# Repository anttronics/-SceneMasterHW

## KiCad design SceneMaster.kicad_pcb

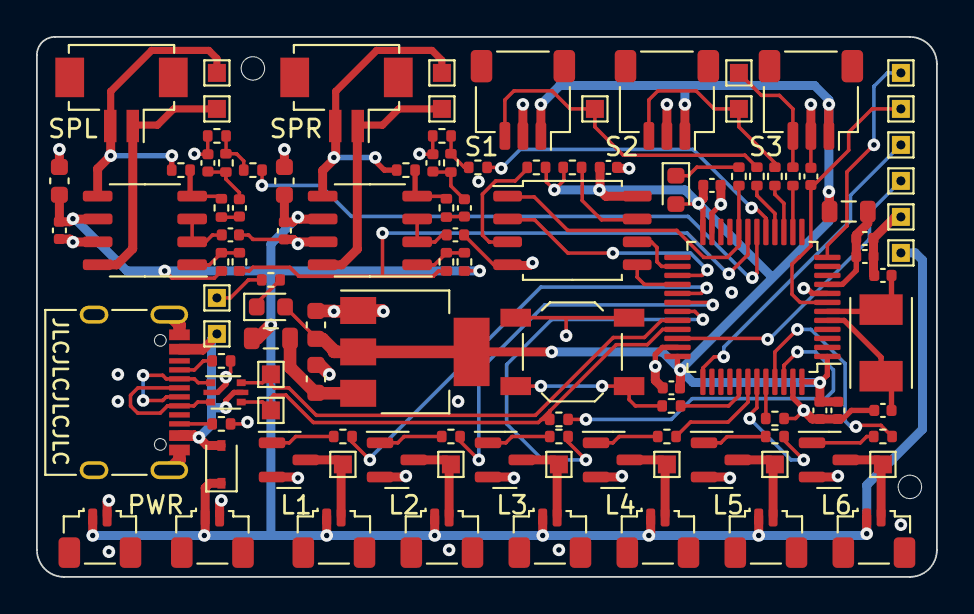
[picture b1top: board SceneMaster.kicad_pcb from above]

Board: 4 copper layers, 50.0 x 30.0 mm, 110 parts (0 on the bottom side), 73 nets.

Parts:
C1, C2: 20p; C_0402_1005Metric
C3, C4, C5, C9, C11, C13, C15: 100n; C_0402_1005Metric
C6, C12: 10u; C_0402_1005Metric
C7: 10n; C_0402_1005Metric
C8, C10: 470n; C_0402_1005Metric
C14, C16, C21, C22: 22u; C_0603_1608Metric
C17, C18, C19, C20: 2.2u; C_0402_1005Metric
D1: 1N5819WS; D_SOD-323
D2: LED Blue; LED_0603_1608Metric
D3: LED Red; LED_0603_1608Metric
FB1, FB2: 100Ω@100MHz; L_0805_2012Metric
J1: TYPE-C-31-M-12; USB_C_Receptacle_XKB_U262-16XN-4BVC11
J2: SPK_R; Hirose_DF13C_CL535-0402-2-51_1x02-1MP_P1.25mm_Vertical
J3: LED1; JST_SUR_SM02B-SURS-TF_1x02-1MP_P0.80mm_Horizontal
J4: LED2; JST_SUR_SM02B-SURS-TF_1x02-1MP_P0.80mm_Horizontal
J5: LED6; JST_SUR_SM02B-SURS-TF_1x02-1MP_P0.80mm_Horizontal
J6: Sensor3; JST_SH_SM03B-SRSS-TB_1x03-1MP_P1.00mm_Horizontal
J7: Sensor1; JST_SH_SM03B-SRSS-TB_1x03-1MP_P1.00mm_Horizontal
J8: Sensor2; JST_SH_SM03B-SRSS-TB_1x03-1MP_P1.00mm_Horizontal
J9: SPK_L; Hirose_DF13C_CL535-0402-2-51_1x02-1MP_P1.25mm_Vertical
J11: PowerIn; JST_SUR_SM02B-SURS-TF_1x02-1MP_P0.80mm_Horizontal
J12: PowerOut; JST_SUR_SM02B-SURS-TF_1x02-1MP_P0.80mm_Horizontal
J13: LED3; JST_SUR_SM02B-SURS-TF_1x02-1MP_P0.80mm_Horizontal
J14: LED4; JST_SUR_SM02B-SURS-TF_1x02-1MP_P0.80mm_Horizontal
J15: LED5; JST_SUR_SM02B-SURS-TF_1x02-1MP_P0.80mm_Horizontal
Q1, Q2, Q3, Q4, Q5, Q6: AO3400A; SOT-23
R1, R2: 5k1; R_0402_1005Metric
R3, R4, R5, R6, R7, R12, R13, R15, R16, R17, R18, R22, R26, R27, R28, R29, R30, R31, R32: 1k5; R_0402_1005Metric
R8, R9: 75R; R_0402_1005Metric
R10, R11, R14, R19, R23: 100k; R_0402_1005Metric
R20, R24: 20k; R_0402_1005Metric
R21, R25: 33k; R_0402_1005Metric
SW1: BUT0; SW_SPST_TL3342
TP1: SENS1; TestPoint_Pad_1.0x1.0mm
TP2: SENS2; TestPoint_Pad_1.0x1.0mm
TP3: SWDIO; TestPoint_THTPad_1.0x1.0mm_Drill0.5mm
TP4: SWCLK; TestPoint_THTPad_1.0x1.0mm_Drill0.5mm
TP5: UARTTX; TestPoint_THTPad_1.0x1.0mm_Drill0.5mm
TP6: D-; TestPoint_Pad_1.0x1.0mm
TP7: D+; TestPoint_Pad_1.0x1.0mm
TP8: VBUS; TestPoint_THTPad_1.0x1.0mm_Drill0.5mm
TP9, TP20: GND; TestPoint_THTPad_1.0x1.0mm_Drill0.5mm
TP10: SENS3; TestPoint_Pad_1.0x1.0mm
TP11: LED1; TestPoint_Pad_1.0x1.0mm
TP12: LED2; TestPoint_Pad_1.0x1.0mm
TP13: LED6; TestPoint_Pad_1.0x1.0mm
TP14: SPK_R-; TestPoint_Pad_1.0x1.0mm
TP15: SKP_L-; TestPoint_Pad_1.0x1.0mm
TP16: LED3; TestPoint_Pad_1.0x1.0mm
TP17: LED4; TestPoint_Pad_1.0x1.0mm
TP18: LED5; TestPoint_Pad_1.0x1.0mm
TP19: 5V; TestPoint_THTPad_1.0x1.0mm_Drill0.5mm
TP21: SPK_R+; TestPoint_Pad_1.0x1.0mm
TP22: SKP_L+; TestPoint_Pad_1.0x1.0mm
TP23: NRST; TestPoint_THTPad_1.0x1.0mm_Drill0.5mm
U1: USBLC6-2P6; SOT-666
U2: W25Q128JVS; SOIC-8_5.275x5.275mm_P1.27mm
U3: AMS1117-3.3; SOT-223-3_TabPin2
U4: STM32F103C8T6; LQFP-48_7x7mm_P0.5mm
U5, U6: 8002B_D; SOP-8_3.9x4.9mm_P1.27mm
Y1: 8MHz; Crystal_SMD_TXC_7A-2Pin_5x3.2mm

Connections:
+3.3VA: C7.1, C12.1, FB1.2, U4.9 (VDDA)
+3V3: C3.1, C4.1, C5.1, C6.1, C13.1, C16.1, D2.2 (A), D3.2 (A), FB1.1, J6.1, J7.1, J8.1, R10.2, R11.1, U2.8 (VCC), U3.2 (VO), U4.1 (VBAT), U4.24 (VDD), U4.36 (VDD), U4.48 (VDD)
+5V: C17.2, C19.2, C21.1, C22.1, D1.1 (K), FB2.1, J3.1, J4.1, J5.1, J11.1, J12.1, J13.1, J14.1, J15.1, R19.2, R23.2, TP19.1, U5.6 (VDD), U6.6 (VDD)
/BUT0: R3.2, U4.41 (PB5)
/D+: J1.A6 (D+), J1.B6 (D+), U1.3 (I/O2)
/D-: J1.A7 (D-), J1.B7 (D-), U1.1 (I/O1)
/LED1: R26.2, U4.29 (PA8)
/LED2: R27.2, U4.30 (PA9)
/LED3: R29.2, U4.31 (PA10)
/LED4: R30.2, U4.42 (PB6)
/LED5: R31.2, U4.43 (PB7)
/LED6: R28.2, U4.45 (PB8)
/Line_Out_L: C10.1, C11.1, R9.2
/Line_Out_R: C8.1, C9.1, R8.2
/MISO: U2.2 (DO(IO1)), U4.27 (PB14)
/MOSI: U2.5 (DI(IO0)), U4.28 (PB15)
/MUTE: R15.2, R22.2, U4.19 (PB1)
/NRST: C15.2, TP23.1, U4.7 (NRST)
/OSC_IN: C1.1, U4.5 (PD0), Y1.1
/OSC_OUT: C2.1, U4.6 (PD1), Y1.2
/PWM_AUDIO_L: R6.2, U4.18 (PB0)
/PWM_AUDIO_R: R4.2, U4.17 (PA7)
/SCLK: U2.6 (CLK), U4.26 (PB13)
/SENS1: R16.1, U4.16 (PA6)
/SENS2: R17.1, U4.15 (PA5)
/SENS3: R18.1, U4.14 (PA4)
/SPI_CS: R12.1, U2.1 (~CS), U4.20 (PB2)
/SPK_L+: J9.2, R25.2, TP22.1, U6.5 (OUT+)
/SPK_L-: J9.1, TP15.1, U6.8 (OUT-)
/SPK_R+: J2.2, R21.2, TP21.1, U5.5 (OUT+)
/SPK_R-: J2.1, TP14.1, U5.8 (OUT-)
/SWCLK: TP4.1, U4.37 (PA14)
/SWDIO: TP3.1, U4.34 (PA13)
/UART_TX: TP5.1, U4.12 (PA2)
/USB_DN: TP6.1, U1.6 (I/O1), U4.32 (PA11)
/USB_DP: R32.1, TP7.1, U1.4 (I/O2), U4.33 (PA12)
/USB_EN: R32.2, U4.46 (PB9)
/VBUS: D1.2 (A), J1.A4 (VBUS), J1.A9 (VBUS), J1.B4 (VBUS), J1.B9 (VBUS), TP8.1, U1.5 (VBUS)
GND: C1.2, C2.2, C3.2, C4.2, C5.2, C6.2, C7.2, C9.2, C11.2, C12.2, C13.2, C14.2, C15.1, C16.2, C17.1, C18.1, C19.1, C20.1, C21.2, C22.2, J1.A1 (GND), J1.A12 (GND), J1.B1 (GND), J1.B12 (GND), J1.S1 (SHIELD), J6.2, J7.2, J8.2, J11.2, J12.2, Q1.2 (S), Q2.2 (S), Q3.2 (S), Q4.2 (S), Q5.2 (S), Q6.2 (S), R1.2, R2.1, R5.1, R7.1, R13.1, R14.2, SW1.2, TP9.1, TP20.1, U1.2 (GND), U2.4 (GND), U3.1 (GND), U4.8 (VSSA), U4.23 (VSS), U4.35 (VSS), U4.47 (VSS), U5.7 (GND), U6.7 (GND)
unnamed: C8.2, R20.2
unnamed: C10.2, R24.2
unnamed: C14.1, FB2.2, U3.3 (VI)
unnamed: C18.2, U5.2 (Bypass), U5.3 (IN+)
unnamed: C20.2, U6.2 (Bypass), U6.3 (IN+)
unnamed: D2.1 (K), R12.2
unnamed: D3.1 (K), R13.2
unnamed: J1.A5 (CC1), R1.1
unnamed: J1.B5 (CC2), R2.2
unnamed: J3.2, Q1.3 (D), TP11.1
unnamed: J4.2, Q2.3 (D), TP12.1
unnamed: J5.2, Q3.3 (D), TP13.1
unnamed: J6.3, R18.2, TP10.1
unnamed: J7.3, R16.2, TP1.1
unnamed: J8.3, R17.2, TP2.1
unnamed: J13.2, Q4.3 (D), TP16.1
unnamed: J14.2, Q5.3 (D), TP17.1
unnamed: J15.2, Q6.3 (D), TP18.1
unnamed: Q1.1 (G), R26.1
unnamed: Q2.1 (G), R27.1
unnamed: Q3.1 (G), R28.1
unnamed: Q4.1 (G), R29.1
unnamed: Q5.1 (G), R30.1
unnamed: Q6.1 (G), R31.1
unnamed: R3.1, SW1.1
unnamed: R4.1, R5.2, R8.1
unnamed: R6.1, R7.2, R9.1
unnamed: R10.1, U2.3 (IO2)
unnamed: R11.2, U2.7 (IO3)
unnamed: R14.1, U4.44 (BOOT0)
unnamed: R15.1, R19.1, U5.1 (~SD)
unnamed: R20.1, R21.1, U5.4 (IN-)
unnamed: R22.1, R23.1, U6.1 (~SD)
unnamed: R24.1, R25.1, U6.4 (IN-)

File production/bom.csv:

Designator,Footprint,Quantity,Value,LCSC Part #
C1,0402,1,20p,C1554
C10,0402,1,2.2u,C12530
C11,0402,1,100n,C1525
C12,0402,1,10u,C15525
C13,0402,1,100n,C1525
C14,0603,1,22u,C59461
C15,0402,1,100n,C1525
C16,0603,1,22u,C59461
C17,0402,1,2.2u,C12530
C18,0402,1,2.2u,C12530
C19,0402,1,2.2u,C12530
C2,0402,1,20p,C1554
C20,0402,1,2.2u,C12530
C21,0603,1,22u,C59461
C22,0603,1,22u,C59461
C3,0402,1,100n,C1525
C4,0402,1,100n,C1525
C5,0402,1,100n,C1525
C6,0402,1,10u,C15525
C7,0402,1,10n,C15195
C8,0402,1,2.2u,C12530
C9,0402,1,100n,C1525
D1,D_SOD-323,1,1N5819WS,C191023
D2,0603,1,LED Blue,C72041
D3,0603,1,LED Red,C2286
FB1,0805,1,100Ω@100MHz,C1015
FB2,0805,1,100Ω@100MHz,C1015
J1,USB_C_Receptacle_XKB_U262-16XN-4BVC11,1,TYPE-C-31-M-12,C165948
J10,SOIC_clipProgSmall,1,Conn_01x08_Male,
J11,JST_SUR_SM02B-SURS-TF_1x02-1MP_P0.80mm_Horizontal,1,PowerIn, C2845343
J12,JST_SUR_SM02B-SURS-TF_1x02-1MP_P0.80mm_Horizontal,1,PowerOut, C2845343
J13,JST_SUR_SM02B-SURS-TF_1x02-1MP_P0.80mm_Horizontal,1,LED3, C2845343
J14,JST_SUR_SM02B-SURS-TF_1x02-1MP_P0.80mm_Horizontal,1,LED4, C2845343
J15,JST_SUR_SM02B-SURS-TF_1x02-1MP_P0.80mm_Horizontal,1,LED5, C2845343
J2,Hirose_DF13C_CL535-0402-2-51_1x02-1MP_P1.25mm_Vertical,1,SPK_R,C2905009
J3,JST_SUR_SM02B-SURS-TF_1x02-1MP_P0.80mm_Horizontal,1,LED1, C2845343
J4,JST_SUR_SM02B-SURS-TF_1x02-1MP_P0.80mm_Horizontal,1,LED2, C2845343
J5,JST_SUR_SM02B-SURS-TF_1x02-1MP_P0.80mm_Horizontal,1,LED6, C2845343
J6,JST_SH_SM03B-SRSS-TB_1x03-1MP_P1.00mm_Horizontal,1,Sensor3,C2936213
J7,JST_SH_SM03B-SRSS-TB_1x03-1MP_P1.00mm_Horizontal,1,Sensor1,C2936213
J8,JST_SH_SM03B-SRSS-TB_1x03-1MP_P1.00mm_Horizontal,1,Sensor2,C2936213
J9,Hirose_DF13C_CL535-0402-2-51_1x02-1MP_P1.25mm_Vertical,1,SPK_L,C2905009
"Q1, Q2, Q3, Q4, Q5, Q6",SOT-23,6,AO3400A, C20917
R1,0402,1,5k1,C25905
R10,0402,1,100k,C25741
R11,0402,1,100k,C25741
R12,0402,1,1k,C11702
R13,0402,1,1k,C11702
R14,0402,1,100k,C25741
R15,0402,1,1k,C11702
R16,0402,1,1k,C11702
R17,0402,1,1k,C11702
R18,0402,1,1k,C11702
R19,0402,1,100k,C25741
R2,0402,1,5k1,C25905
R20,0402,1,20k,C25765
R21,0402,1,20k,C25765
R22,0402,1,1k,C11702
R23,0402,1,100k,C25741
R24,0402,1,20k,C25765
R25,0402,1,20k,C25765
R3,0402,1,1k,C11702
R4,0402,1,1k,C11702
R5,0402,1,1k,C11702
R6,0402,1,1k,C11702
R7,0402,1,1k,C11702
R8,0402,1,75R,C25905
R9,0402,1,75R,C25905
SW1,SW_SPST_TL3342,1,BUT0,C318884
TP1,TestPoint_Pad_1.0x1.0mm,1,SENS1,
TP10,TestPoint_Pad_1.0x1.0mm,1,SENS3,
TP11,TestPoint_Pad_1.0x1.0mm,1,LED1,
TP12,TestPoint_Pad_1.0x1.0mm,1,LED2,
TP13,TestPoint_Pad_1.0x1.0mm,1,LED6,
TP14,TestPoint_Pad_1.0x1.0mm,1,SPK_R-,
TP15,TestPoint_Pad_1.0x1.0mm,1,SKP_L-,
TP16,TestPoint_Pad_1.0x1.0mm,1,LED3,
TP17,TestPoint_Pad_1.0x1.0mm,1,LED4,
TP18,TestPoint_Pad_1.0x1.0mm,1,LED5,
TP2,TestPoint_Pad_1.0x1.0mm,1,SENS2,
TP21,TestPoint_Pad_1.0x1.0mm,1,SPK_R+,
TP22,TestPoint_Pad_1.0x1.0mm,1,SKP_L+,
TP6,TestPoint_Pad_1.0x1.0mm,1,D-,
TP7,TestPoint_Pad_1.0x1.0mm,1,D+,
TP8,TestPoint_THTPad_1.0x1.0mm_Drill0.5mm,1,VBUS,
TP9,TestPoint_THTPad_1.0x1.0mm_Drill0.5mm,1,GND,
U1,SOT-666,1,USBLC6-2P6,C2827693
U2,SOIC-8_5.275x5.275mm_P1.27mm,1,W25Q128JVS,C97521
U3,SOT-223-3_TabPin2,1,AMS1117-3.3,C6186
U4,LQFP-48_7x7mm_P0.5mm,1,STM32F103C8T6, C8734
"U5, U6",SOP-8_3.9x4.9mm_P1.27mm,2,8002B_D,C329450
Y1,Crystal_SMD_TXC_7A-2Pin_5x3.2mm,1,8MHz,C115962

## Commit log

2023-02-05 Change sensor & speaker connectors to 1mm SH
2023-02-11 Resize some vias to 0.7/0.3
2023-02-12 First SGGS re-route
2023-03-27 Last changes before prototype run
2023-04-11 Add gate resistor to mosfets
2023-04-12 Add USB enable pull up
2023-12-20 Change programming port
2023-12-20 cleanup according to gitignore
2023-12-21 add license

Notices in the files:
SceneMaster.kicad_pcb:
SPDX-FileCopyrightText: 2023 Antonios Vamporakis
SPDX-License-Identifier: CERN-OHL-W-2.0+
using it under the terms of the CERN-OHL-W v2 (https:/cern.ch/cern-ohl).
As per CERN-OHL-W v2 section 4.1, should You produce hardware based on
